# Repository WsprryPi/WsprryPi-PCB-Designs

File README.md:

# WsprryPi PCB Designs

KiCad schematics, PCB layouts, local libraries, and engineering documentation for WsprryPi and Raspberry Pi Pico projects.

See each project's order status, assembly requirements, and validation limits before fabrication. KiCad source files are authoritative; included PDFs are reference exports and may not match the current sources.

## Experimental use and warranty

All designs are provided **as is, without warranty**, as stipulated by the [MIT license](LICENSE.md) for repository-owned work. These are experimental hardware systems. They should not be used for production work unless the operator understands the design's limitations, assembly and power requirements, calibration needs, and the validation required for the actual system and operating conditions.

The operator is responsible for determining suitability and verifying the assembled hardware. A clean CAD check or a fabrication-ready layout does not establish electrical, RF, thermal, mechanical, or system performance. Third-party assets retain their documented licenses and notices.

## Projects

| Project | Purpose | Status / reference export |
| --- | --- | --- |
| [WsprryPi LPF](WsprryPi%20LPF/README.md) | Low-pass filter board and design workbook | Export from the KiCad source |
| [WsprryPi LPF-LCL](WsprryPi%20LPF-LCL/README.md) | Five-element L-first LPF with minimum-loss WSPR/QRSS tuning | Independent routed development board; physical/RF qualification pending |
| [Relay-Switched LPF](Relay-Switched%20LPF/README.md) | Independent reconstruction of the QRP Labs Rev. 5 five-filter relay carrier | Schematic and two-layer PCB; unqualified, see project validation |
| [Pico 2W Wattmeter Shield](Pico%202W%20Wattmeter%20Shield/README.md) | ADL5904 RF detector and ADS1115 ADC shield | See project assembly drawings |
| [Pico 2W Shield Template](Pico%202W%20Shield%20Template/README.md) | Unwired shield interface, outline, and antenna notch | KiCad project template |
| [Logic RF Driver](Logic%20RF%20Driver/README.md) | Compact SN74LVC2T45 clock driver with paralleled outputs | Routed two-layer prototype for the 137 kHz–145 MHz target; RF performance unqualified |
| [RF Indicator LED](RF%20Indicator%20LED/README.md) | RF indicator circuit draft | Incomplete component selection; empty PCB, see project validation |
| [Quad Logic Buffer Amp](Quad%20Logic%20Buffer%20Amp/README.md) | Logic buffer RF amplifier schematic | Standalone 80 × 30 mm estimated PCB, placed and unrouted |
| [WsprryPico Quad Logic Buffer Amp](WsprryPico%20Quad%20Logic%20Buffer%20Amp/README.md) | Independent Pico shield copy of Quad Logic Buffer Amp with project-local libraries | Placement review pending, unrouted |
| [WsprryPi Quad Logic Buffer Amp](WsprryPi%20Quad%20Logic%20Buffer%20Amp/README.md) | Raspberry Pi Zero HAT logic buffer amplifier with local LPF header assets | Placement review pending, unrouted |
| [WsprryPico GPIO Shield with GPS](WsprryPico%20GPIO%20Shield%20with%20GPS/README.md) | Direct Pico GP2 BS170 RF amplifier with onboard GNSS and independent local libraries | Placed and routed GPIO/GNSS design; see current validation |
| [WsprryPico GPIO Shield with GPS - Torroid Edition](WsprryPico%20GPIO%20Shield%20with%20GPS%20-%20Torroid%20Edition/README.md) | GPIO amplifier with a bifilar transformer | Placed and routed within the original outline; all SMT on the underside; physical/RF qualification pending |
| [WsprryPico Synth Shield with GPS](WsprryPico%20Synth%20Shield%20with%20GPS/README.md) | Pico 2 W TCXO/Si5351A shield with a BS170 amplifier and onboard GNSS | Implemented PCB for the 2200 m–10 m target; see current validation and bias setup |
| [QRP Labs Modules](QRP%20Labs%20Modules/README.md) | Electrical models of the photographed 25 MHz TCXO and Rev6 synthesizer, with their interconnection | [Reference schematic PDF](QRP%20Labs%20Modules/QRP%20Labs%20Modules.pdf); separate from the proposed synth shield |
| [RPi Full-Size HAT Template](RPi%20Full-Size%20HAT%20Template/README.md) | Official full-size HAT geometry and complete 40-pin interface | KiCad project template |
| [RPi Zero HAT Template](RPi%20Zero%20HAT%20Template/README.md) | Zero-size uHAT geometry and complete HAT+ capable 40-pin interface | KiCad project template |
| [WsprryPi Zero GPIO BS170](WsprryPi%20Zero%20GPIO%20BS170/README.md) | Zero-size Raspberry Pi GPIO RF amplifier with a single BS170 | **Ready for order:** headers and BS170 fitted by hand after manufacture; see [fabrication and assembly notes](WsprryPi%20Zero%20GPIO%20BS170/FABRICATION-NOTES.md) |

[Project-local Pico 2 W library assets](Pico%202W%20Wattmeter%20Shield/pico-2w-libs/README.md) include a symbol, footprints, and STEP model with documented compatibility and provenance limits. They are stored inside the Wattmeter Shield project; the Shield Template uses its own independent local libraries.

## Open a design

Clone [WsprryPi/WsprryPi-PCB-Designs](https://github.com/WsprryPi/WsprryPi-PCB-Designs) into a folder named `WsprryPi PCB Designs` and open the project's `.kicad_pro` file in KiCad. Read its README for assembly requirements, dependencies, and validation limits. Follow the applicable template's instructions to create a new shield or HAT project.

| Project | Saved schematic and PCB generator version |
| --- | --- |
| WsprryPi LPF, WsprryPi LPF-LCL, Pico 2W Wattmeter Shield, Pico 2W Shield Template, Logic RF Driver, RF Indicator LED, Quad Logic Buffer Amp, WsprryPico Quad Logic Buffer Amp, WsprryPi Quad Logic Buffer Amp, WsprryPico GPIO Shield with GPS, WsprryPico GPIO Shield with GPS - Torroid Edition, WsprryPico Synth Shield with GPS, RPi Full-Size HAT Template, RPi Zero HAT Template, WsprryPi Zero GPIO BS170 | KiCad 10.0 |

Project library tables use `${KIPRJMOD}` paths. Keep each project's local libraries together when copying it. The Pico and HAT projects use their own local libraries and installed KiCad models where their project documentation specifies them.

### Project-local libraries

The LPF includes local copies of its symbols and footprints, plus available STEP models, resolved through `${KIPRJMOD}`. Its local library assets require KiCad 10.0.1 or newer; the generator version above describes its saved format. The other projects maintain their own independent local libraries as described in their READMEs.

- [LPF library contents and limits](WsprryPi%20LPF/libraries/README.md)
- [BS170 amplifier library sources and limits](WsprryPi%20Zero%20GPIO%20BS170/LIBRARY-SOURCES.md)

Project documentation records model gaps, assembly exclusions, and the applicability of ERC/DRC findings to the identified source revision. Order readiness does not establish measured electrical, thermal, or RF performance.

## Design proposals

These documents describe proposed circuits and outstanding engineering requirements; they do not establish implemented or validated hardware.

- [GPS frequency calibration for Pi and Pico](design/GPS-FREQUENCY-CALIBRATION.md): LS7366R capture of Si5351 CLK2 against GPS PPS.
- [Broadband RF amplifier HAT](design/raspberry-pi-hat-broadband-rf-amplifier.md): a proposed clock-input amplifier, power control, and supply architecture.

## Repository contents

Track design sources, local libraries, reusable models, design calculations, intentional reference exports, and documentation. Preserve legacy cache or rescue libraries required by a design.

The root [`.gitignore`](.gitignore) covers KiCad local preferences, locks, caches, automatic backups, `.history`, and `jlcpcb/` plugin state and output throughout the repository. Put regenerable exports in `generated/`, `production/`, or `fabrication/`.

Publish manufacturing packages with the corresponding GitHub release, identifying the source commit, board revision, KiCad version, and validation status. Keep assembly and fabrication requirements in the project's maintained documentation.

## Contributions and license

See [CONTRIBUTING.md](CONTRIBUTING.md) for editing and validation requirements. Report problems through [GitHub Issues](https://github.com/WsprryPi/WsprryPi-PCB-Designs/issues). [AGENTS.md](AGENTS.md) contains shared agent guidance; [CLAUDE.md](CLAUDE.md) points to it.

Repository-owned work uses the [MIT license](LICENSE.md). Preserve third-party copyright, attribution, and license terms; project and library documentation identifies known exceptions and provenance limits.

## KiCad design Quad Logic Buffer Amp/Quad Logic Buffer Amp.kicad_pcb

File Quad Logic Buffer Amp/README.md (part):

# Quad Logic Buffer Amp

The drawing uses native symbols, 375 wire segments, branch junctions, and common VDD and GND power symbols. J2 and R6 connect the isolated output return to circuit ground as drawn. U1, U2, U4, and U5 use the reference symbol layout and the local TSSOP-20 footprint. The printed supplier code C6930 identifies [TI SN74ACT244PWR](https://www.lcsc.com/product-detail/C6930.html). The connector and RGB LED symbols reproduce the visible terminal functions. Their physical pin assignments and package selections are recorded below.

## Standalone PCB

The [PCB](Quad%20Logic%20Buffer%20Amp.kicad_pcb) uses an estimated **80 × 30 mm** rectangular outline. The finished instrument is specified as 85 × 30 × 45 mm. Page 4 shows the bare board nearly overhead. In a 1,650-pixel-high rendering, the board spans about 670 × 255 pixels and the USB-C shell spans about 75 pixels. Using the selected shell’s 8.94 mm nominal width gives about 80 × 30.4 mm. The roughly 2.6:1 board aspect ratio also matches the chosen outline. Shell variation, perspective, and edge selection limit the estimate to a few millimetres. The photo shows no distinct mounting holes. The PCB has a 1 mm fillet at each corner. [Product specifications](https://turnislandsystems.com/product/tis-1w-digital-1w-power-amplifier/) · [Board photograph and rendering, page 4](https://turnislandsystems.com/wp-content/uploads/2025/09/TIS-1W.pdf#page=4)

## Independent local library

The [symbol table](sym-lib-table) and [footprint table](fp-lib-table) register `logic-buffer-amp`. Every library and assigned 3D-model path uses `${KIPRJMOD}`; neither source project nor an installed KiCad 3D-model library is needed to resolve these copied assets.

- [Symbol library](logic-buffer-amp.kicad_sym): unused template symbols `Raspberry_Pi_Pico_2W` and `Socket_1x20_P2.54mm_BOM`, plus synth-shield `C`, `GND`, `L`, `LED`, `PWR_FLAG`, `R`, and `SMA`, and a standalone `SN74ACT244`.
- [Footprint library](logic-buffer-amp.pretty/): the template header and all synth-shield capacitor, inductor, LED, resistor, and SMA footprint variants listed below, plus the TSSOP-20 buffer footprint.
- [3D models](logic-buffer-amp.3dshapes/README.md): twenty-three local assets, including local copies of the standard models referenced by the synth shield.
- [Sources, terms, and limitations](LIBRARY-SOURCES.md) and [asset manifest](LIBRARY-MANIFEST.json).

| Symbol | Available local footprints |
| --- | --- |
| Raspberry_Pi_Pico_2W | Raspberry_Pi_Pico_2W_Header |
| Socket_1x20_P2.54mm_BOM | None; schematic-only purchasing description |
| C | C_0603_1608Metric, C_0805_2012Metric, C_1206_3216Metric |
| L | L_0603_1608Metric, L_TDK_VLS6045EX_VLS6045AF |
| LED | LED_0603_1608Metric |
| R | R_0603_1608Metric, R_1210_3225Metric |
| SMA | SMA_Adafruit_1865_EdgeMount |
| SN74ACT244 | TSSOP-20_4.4x6.5mm_P0.65mm (TI PW package) |
| GND, PWR_FLAG | None; schematic-only power symbols |

The `SN74ACT244` symbol defaults to the local TSSOP-20 footprint for **SN74ACT244PWR** (TI PW package, 4.4 x 6.5 mm body, 0.65 mm pitch). Its 20 pin names and electrical types were checked against [TI SCAS517G, page 3](https://www.ti.com/lit/ds/symlink/sn74act244.pdf#page=3). The installed KiCad 74HC244 graphics were adapted into a standalone ACT definition, with TI pin naming and datasheet; this is not a simulation model. Other imported symbols retain their source defaults. Assign the appropriate `logic-buffer-amp` footprint when placing a component; generic symbols do not select a particular physical part. The placed schematic assignments and remaining package decisions are listed below.

## Footprints and models

All 65 physical references, including five paired test-point footprints providing ten probe pads, have project-local footprints. The schematic-only power symbols are outside this count. KiCad 10.0.6 netlist verification confirmed that every assigned symbol has the same set of pin numbers as the footprint pads and that every populated package resolves to a local model. The ten bare test pads have no component body. The footprint update preserved net connectivity.

| Assigned references | Local package and model |
| --- | --- |
| C2, all 100 nF capacitors, and all 0603 resistors | See the [passive BOM](#passive-bom) below. |
| U1, U2, U4, U5 | TI PW TSSOP-20, matching KiCad package STEP |
| L1 | Murata BLM18PG121SN1D, 0603 power-line ferrite bead, 120 Ω ±25% at 100 MHz, 2 A through 85 °C, 50 mΩ maximum initial DC resistance. LCSC reported 832,350 units on 2026-11-18. [LCSC C14709](https://www.lcsc.com/product-detail/C14709.html) · [Murata specification](https://pim.murata.com/asset/pim4/ferriteBeadInductortypefilter/ENFA2345_PDF_FERRITEBEADINDUCTORTYPEFILTER) |
| J5, J6 | Adafruit product 1865 female edge-launch SMA for a 1.6 mm board. Both connectors are on hand. Local VRML is an illustrative preview. [Connector specification](https://www.adafruit.com/product/1865) |
| J1, J2 | Vertical 1×2 through-hole pin header on 2.54 mm pitch, with the Zero GPIO BS170 shield’s footprint and STEP model |
| Z6 | Nexperia PESD5V0U1UA,115 in SOD323. Pad 1 is cathode and pad 2 is anode. [Manufacturer pinning](https://assets.nexperia.com/documents/data-sheet/PESD5V0U1UA.pdf) |
| R9 | Panasonic ERJP14J510U, 51 Ω, ±5%, 0.5 W rated, 1210. The permissible continuous input depends on board temperature and derating. [Manufacturer specifications](https://industrial.panasonic.com/tw/products/pt/small-and-high-power-chip-resistors/models/ERJP14J510U) |
| TP22, TP4, TP21, TP10, TP6 | [Paired probe footprint](logic-buffer-amp.pretty/TestPoint_Pair_P2.54mm_Drill0.5mm.kicad_mod) with two of the same pads at a fixed 2.54 mm pitch. Each pair uses one reference. Schematic units A and B correspond to pads 1 and 2. TP22 is USB5V/GND (formerly TP22/TP3), TP4 is D+/D− (formerly TP4/TP5), and TP21 is VDD/GND (formerly TP21/TP19). TP10 is RF input/GND (formerly TP10/TP16). TP6 is RF output/GND_OUT (formerly TP6/TP7). On each RF pair, pad 1 is toward the rear and pad 2 is toward the SMA edge. |
| U6 | TI SN74LVC2G14DCKR, six-pin SC70. Inputs 1/3, outputs 6/4, GND 2, VCC 5. [TI pinout](https://www.ti.com/lit/ds/symlink/sn74lvc2g14.pdf) |
| U88 | TI SN74LVC1G00DCKR, five-pin SC70. Inputs 1/2, GND 3, output 4, VCC 5. [TI pinout](https://www.ti.com/lit/ds/symlink/sn74lvc1g00.pdf) |
| U8, U59 | TI SN74LVC2G04DCKR, six-pin SC70. Inputs 1/3, outputs 6/4, GND 2, VCC 5. [TI pinout](https://www.ti.com/lit/ds/symlink/sn74lvc2g04.pdf) |
| D3 | Diodes Incorporated 1N4148W-7-F in SOD-123. Banded cathode on pad 1, anode on pad 2. [Manufacturer datasheet](https://www.diodes.com/datasheet/download/1N4148W.pdf) |
| Q3 | onsemi MMBT3904LT1G, SOT-23. Base 1, emitter 2, collector 3. [onsemi pinout](https://www.onsemi.com/pdf/datasheet/mmbt3904lt1-d.pdf) |
| Q6 | Vishay Si2343DS-T1-GE3, SOT-23. Gate 1, source 2, drain 3. [Vishay pinout](https://www.vishay.com/docs/72079/si2343ds.pdf) |

### Passive BOM

Quantities are per board. Both Samsung capacitor types are X7R, ±10%, 50 V DC. C2 is a 1206 bulk capacitor on the 5 V rail after L1. The twelve general-purpose 100 nF positions use Samsung 0603 X7R capacitors. The four bridge coupling capacitors use Walsin 1206 C0G/NP0, ±5%, 50 V DC. The thirteen 0603 resistors are UNI-ROYAL thick film, ±1%, 100 mW, 75 V maximum working voltage, and ±100 ppm/°C. Both power and voltage limits apply. R9 uses the separately specified 0.5 W 1210 input termination. Stock was checked at LCSC on 2026-11-18.

| References | Qty | Value | Manufacturer part number | LCSC | Stock |
| --- | ---: | --- | --- | --- | ---: |
| C2 | 1 | 1 µF | CL31B105KBHNNNE | [C1848](https://www.lcsc.com/product-detail/C1848.html) | 141,650 |
| C5–C7, C9, C14, C15, C21, C22, C34, C127, C128, C160 | 12 | 100 nF | CL10B104KB8NNNC | [C1591](https://www.lcsc.com/product-detail/C1591.html) | 214,300 |
| C10–C13 | 4 | 100 nF | 1206N104J500CT | [C170182](https://www.lcsc.com/product-detail/C170182.html) | 119,055 |
| R2, R3 | 2 | 51 Ω | 0603WAF510JT5E | [C23197](https://www.lcsc.com/product-detail/C23197.html) | 650,600 |
| R37 | 1 | 100 Ω (production marking 01A) | TBD | — | — |
| R30, R31 | 2 | 5.1 kΩ | 0603WAF5101T5E | [C23186](https://www.lcsc.com/product-detail/C23186.html) | 13,449,700 |
| R4, R5, R8, R13, R19, R36 | 6 | 10 kΩ | 0603WAF1002T5E | [C25804](https://www.lcsc.com/product-detail/C25804.html) | 2,287,600 |
| R10 | 1 | 100 kΩ | 0603WAF1003T5E | [C25803](https://www.lcsc.com/product-detail/C25803.html) | 4,436,200 |
| R6 | 1 | 1 MΩ | 0603WAF1004T5E | [C22935](https://www.lcsc.com/product-detail/C22935.html) | 2,087,900 |

C10/C11 and C12/C13 are the two bridge coupling pairs. At 1 W into 50 Ω, the ideal 1:2 transformer reflects 12.5 Ω and carries 0.283 A RMS of load current in its primary. Each matched parallel pair splits that current, giving 0.141 A RMS per capacitor. As a design check, 0.25 A RMS per capacitor allows margin for magnetizing current and unequal sharing. At 1 MHz the two 200 nF pairs contribute about 1.59 Ω of ideal series reactance around the loop.

The bridge uses a Class I C0G dielectric for capacitance stability and low dielectric loss. Verify loaded output and capacitor temperature with these parts at the intended duty cycle across 1–60 MHz.

L1 sits between the protected USB supply at Q6 and the amplifier VDD rail, with C14 on the input side and C2 on the load side. The reference amplifier drew 364–400 mA into 50 Ω at the three documented frequencies (1, 10, and 60 MHz) and 488 mA into 25 Ω at 10 MHz. At 488 mA, the maximum initial DC resistance gives a 24.4 mV drop and 11.9 mW of DC loss. Murata’s typical impedance curve rises from a few ohms at 1 MHz to roughly 40 Ω at 10 MHz and 100 Ω at 60 MHz. This favors isolation of fast driver currents from the USB lead. Actual attenuation depends on DC bias, the capacitors, and the routed board. [Murata impedance curve, page 3](https://datasheet.octopart.com/BLM18PG121SN1D-Murata-datasheet-138707164.pdf#page=3)

The bead body is nominally 1.6 × 0.8 × 0.8 mm. The project’s generic 0603 pattern and Murata’s reflow pattern both have a 0.70 mm inner gap. The project uses a 2.45 mm outer span and 0.95 mm pad width, compared with Murata’s 2.0 mm span and 0.7 mm exposed width. The current rating and DC-drop calculation apply to the bead. The local STEP is a nominal package preview. [Murata mounting drawing, page 9](https://pim.murata.com/asset/pim4/ferriteBeadInductortypefilter/ENFA2345_PDF_FERRITEBEADINDUCTORTYPEFILTER#page=9)

D4 and D5 use CHONGTIAN CT-3210URGBC-P15-2B side-view RGB LEDs. With the lens facing the board edge (local −Y), the four lands read left to right as 1 red, 4 green, 3 blue, and 2 common anode. Both anodes go to VDD. D4 uses blue through R8. The D5 driver connects the two inner cathodes via R15 and R13 as detailed below. The local footprint follows the recommended 3.9 mm land span. The local 3D model represents the nominal body and side lens. LCSC listed 2,450 units on 2026-11-18. [LCSC C52676076](https://www.lcsc.com/product-detail/C52676076.html) · [Manufacturer drawing, PDF page 2](https://datasheet.lcsc.com/datasheet/pdf/34cd5fd2fc904333a2eb28493617a30e.pdf#page=2)

X1 uses the HRO TYPE-C-31-M-12 horizontal top-mount USB-C receptacle. The drawing combines A1/B12 and B1/A12 into two ground lands and A4/B9 and B4/A9 into two VBUS lands. A6/B6 are D+, A7/B7 are D−, A5 is CC1, B5 is CC2, and A8/B8 are the open SBU contacts. All four shell stakes use SH on GND. The two locating holes are unplated. The local footprint uses the paired land names in the schematic and a supplier 3D model. LCSC listed 491,060 units on 2026-11-18. [LCSC C165948](https://www.lcsc.com/product-detail/C165948.html) · [Manufacturer drawing](https://datasheet.lcsc.com/datasheet/pdf/9e56b777c022540fcce7c7f67825f55e.pdf)

Page 3 specifies SC70 for U8 and U59. In the page 4 prototype photograph, U6 and U88 have the same apparent body size and lead pitch as those adjacent inverters. The corresponding TI DCK packages preserve the schematic pin numbers. The visible size of D3 relative to Q3 and nearby 0603 passives supports SOD-123. The selected ordering codes are implementation choices for this shield.

### L2 flat-mount transformer

The [four-pad footprint](logic-buffer-amp.pretty/Transformer_BN43-1502_Flat_4Lead.kicad_mod) and [VRML model](logic-buffer-amp.3dshapes/Transformer_BN43-1502_Flat_4Lead.wrl) mount the BN43-1502 flat with both bores parallel to the board. Page 3 specifies an isolated 1:2 turns ratio. Page 4 shows two winding ends emerging at each end of the core. The footprint assigns the primary to the negative-Y end and the secondary to the positive-Y end. Left and right below refer to the top view at zero footprint rotation.

| Pad | Center X, Y (mm) | Winding and schematic connection |
| --- | --- | --- |
| 1, square | −3.25, −8.75 | Primary, C12.2 and C13.2, also R37.1 |
| 2 | +3.25, −8.75 | Primary, C10.2 and C11.2 |
| 3 | −3.25, +8.75 | Secondary output, TP6 pad 1 and J5 center contact |
| 4 | +3.25, +8.75 | Secondary return, TP6 pad 2 and J5 shield on GND_OUT |

L2 uses the builder-confirmed BN43-1502 with two primary turns and four secondary turns. A 50 Ω secondary load reflects 12.5 Ω to the bridge. Production wire gauge is unknown. The model shows each turn passing through both bores, with separate winding ends at the measured hole positions.

**Winding and installation**

1. Lay the core flat in its footprint orientation. Call the end facing pads 1 and 2 the primary face and the opposite end the secondary face. Label the **whole bore** beside pads 1 and 3 **A**, and the bore beside pads 2 and 4 **B**. Keep these labels fixed when working from the other end. One turn goes out through one bore and returns through the other.
2. **Primary, pad 1 to pad 2:** Leave a tail at pad 1. Feed the wire through A from the primary face to the secondary face, then back through B to the primary face. Repeat that complete path once. The finish exits B beside pad 2.
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
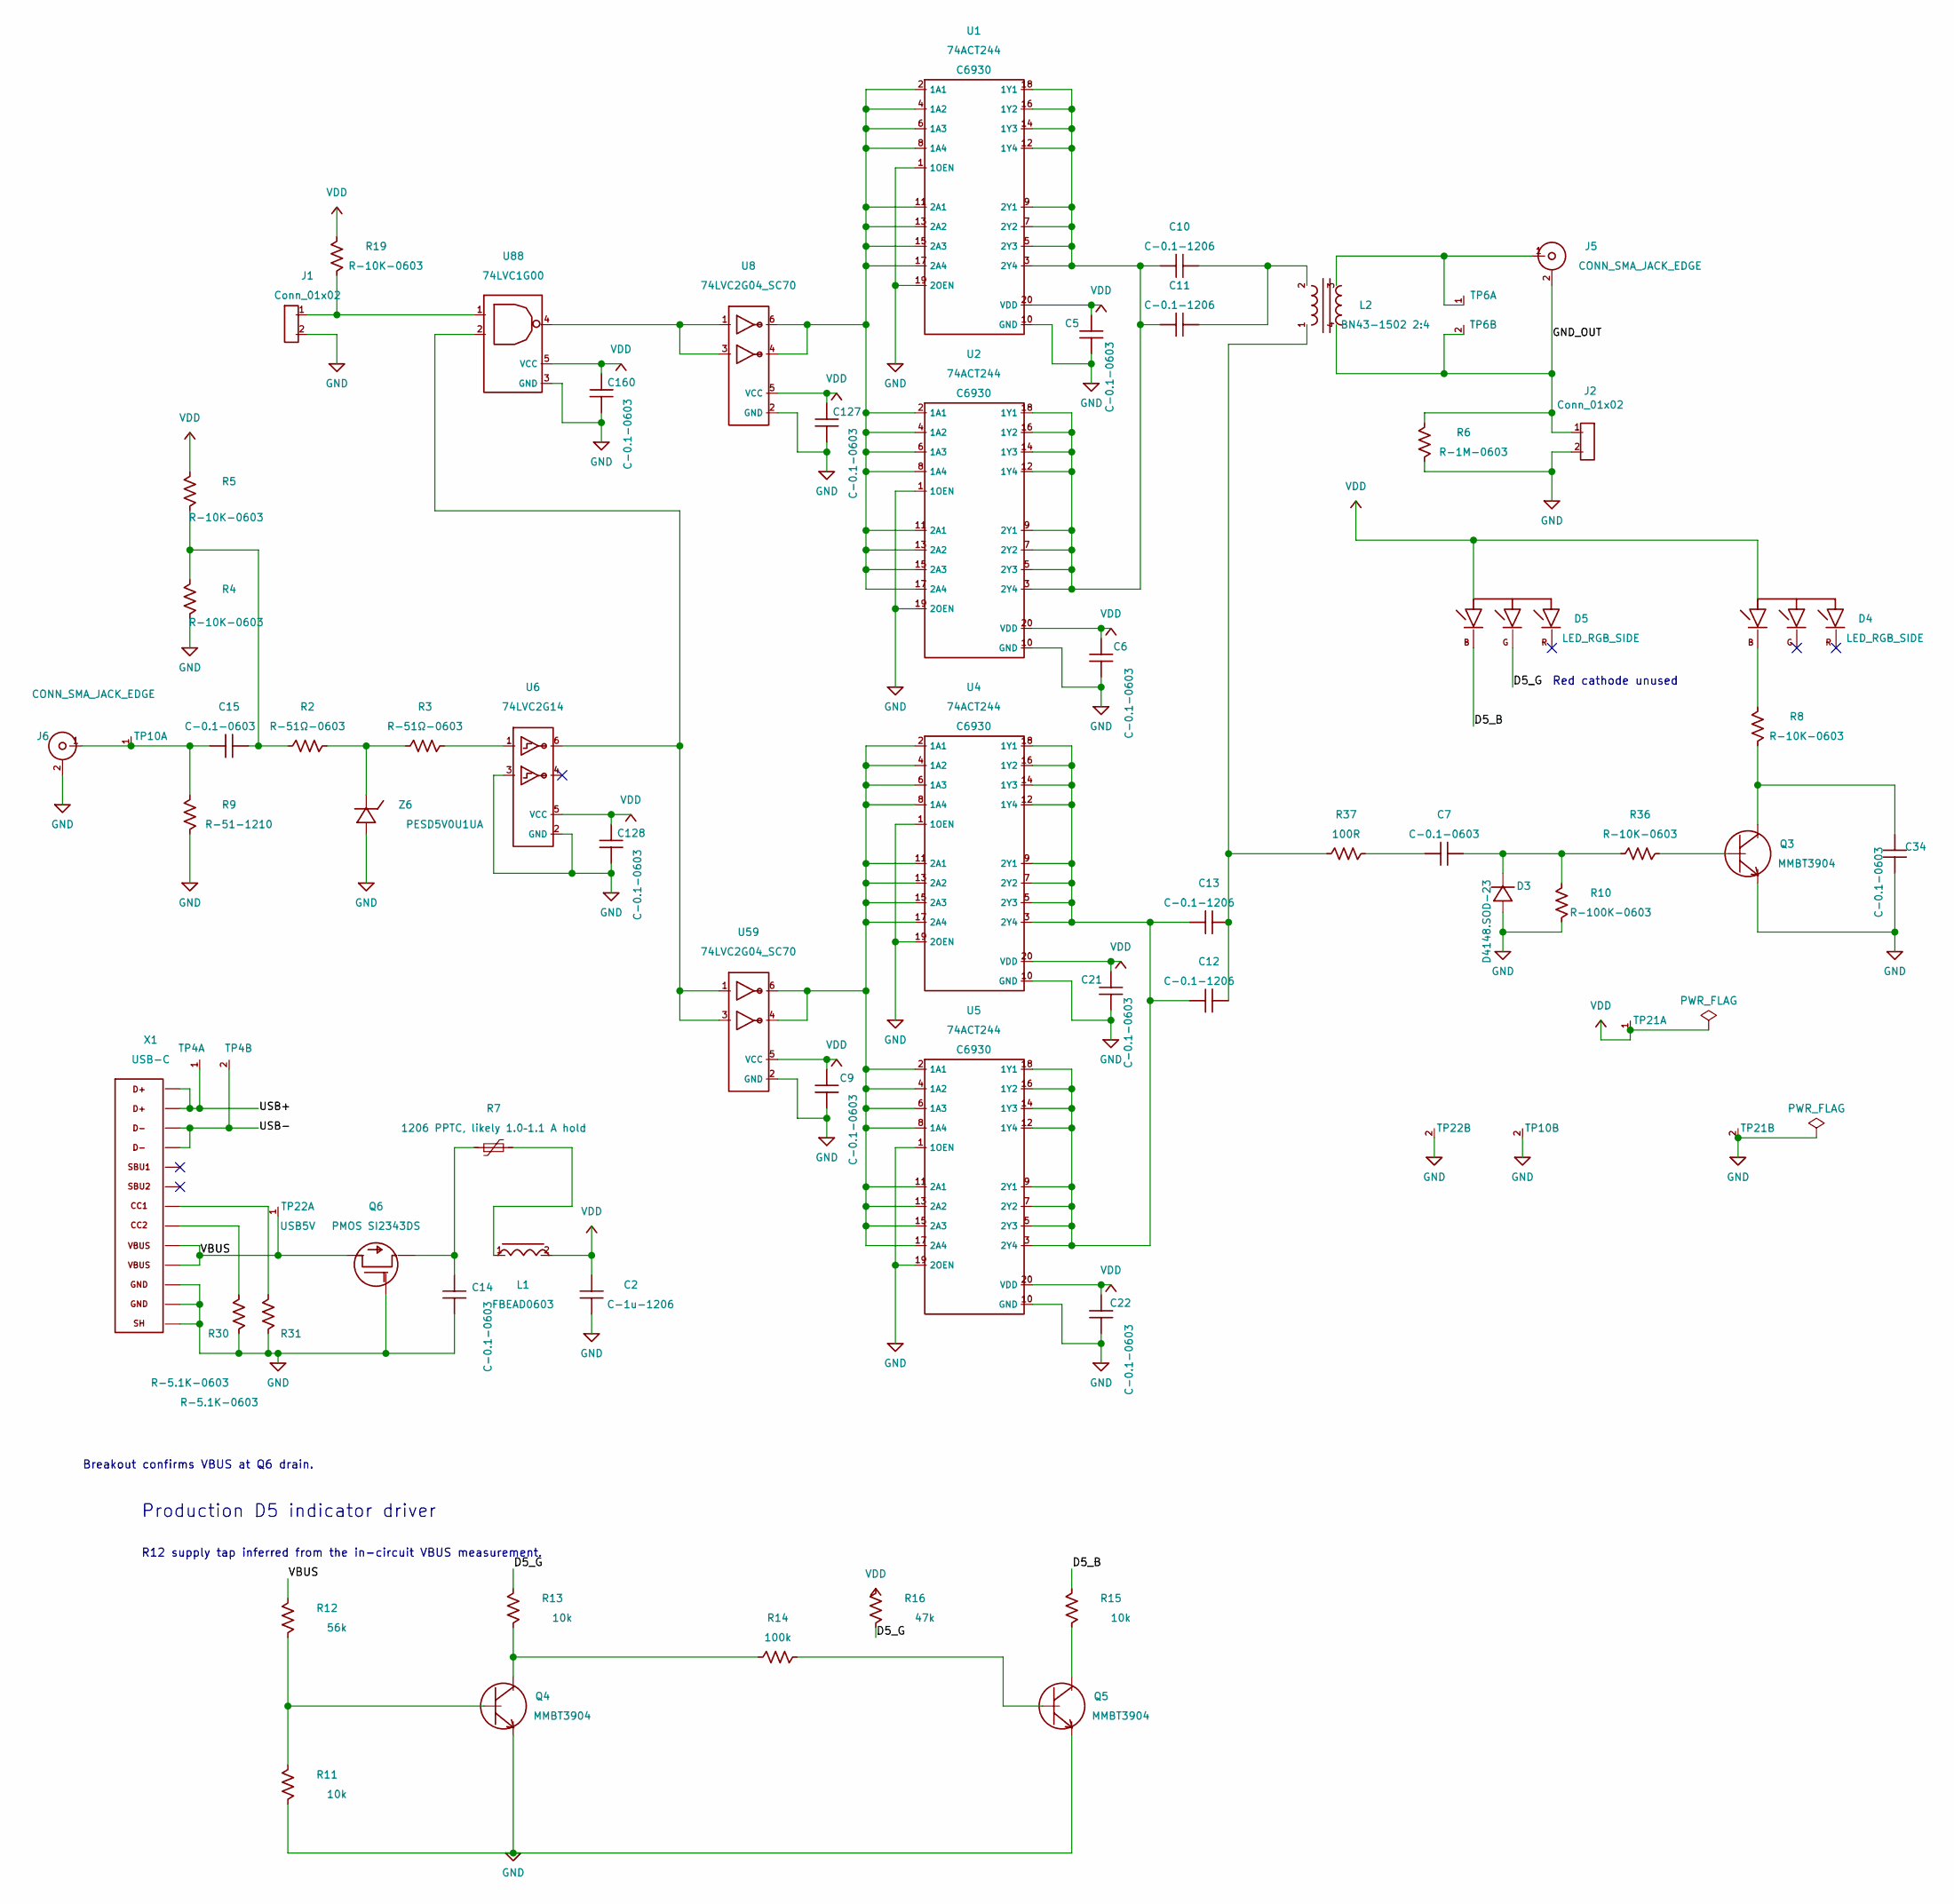
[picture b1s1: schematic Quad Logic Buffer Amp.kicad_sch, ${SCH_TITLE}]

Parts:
C2: C-1u-1206; C_1206_3216Metric; MPN CL31B105KBHNNNE; LCSC C1848
C5, C6, C7, C9, C14, C15, C21, C22, C34, C127, C128, C160: C-0.1-0603; C_0603_1608Metric; MPN CL10B104KB8NNNC; LCSC C1591
C10, C11, C12, C13: C-0.1-1206; C_1206_3216Metric; MPN 1206N104J500CT; LCSC C170182
D3: D4148.SOD-23; D_SOD-123; MPN 1N4148W-7-F
D4, D5: LED_RGB_SIDE; LED_CT-3210URGBC-P15-2B; MPN CT-3210URGBC-P15-2B; LCSC C52676076
J1, J2: Conn_01x02; PinHeader_1x02_P2.54mm_Vertical
J5, J6: CONN_SMA_JACK_EDGE; SMA_Adafruit_1865_EdgeMount
L1: FBEAD0603; L_0603_1608Metric; MPN BLM18PG121SN1D; LCSC C14709
L2: BN43-1502 2:4; Transformer_BN43-1502_Flat_4Lead
Q3: MMBT3904; SOT-23; MPN MMBT3904LT1G
Q4, Q5: MMBT3904; SOT-23
Q6: PMOS SI2343DS; SOT-23; MPN Si2343DS-T1-GE3
R2, R3: R-51Ω-0603; R_0603_1608Metric; MPN 0603WAF510JT5E; LCSC C23197
R4, R5, R8, R19, R36: R-10K-0603; R_0603_1608Metric; MPN 0603WAF1002T5E; LCSC C25804
R6: R-1M-0603; R_0603_1608Metric; MPN 0603WAF1004T5E; LCSC C22935
R7: 1206 PPTC, likely 1.0–1.1 A hold; Fuse_1206_3216Metric
R9: R-51-1210; R_1210_3225Metric; MPN ERJP14J510U
R10: R-100K-0603; R_0603_1608Metric; MPN 0603WAF1003T5E; LCSC C25803
R11, R13, R15: 10k; R_0603_1608Metric; MPN 0603WAF1002T5E; LCSC C25804
R12: 56k; R_0603_1608Metric
R14: 100k; R_0603_1608Metric
R16: 47k; R_0603_1608Metric
R30, R31: R-5.1K-0603; R_0603_1608Metric; MPN 0603WAF5101T5E; LCSC C23186
R37: 100R; R_0603_1608Metric
TP4: USB data; TestPoint_Pair_P2.54mm_Drill0.5mm
TP6: RF output; TestPoint_Pair_P2.54mm_Drill0.5mm
TP10: RF input; TestPoint_Pair_P2.54mm_Drill0.5mm
TP21: VDD/GND; TestPoint_Pair_P2.54mm_Drill0.5mm
TP22: USB5V; TestPoint_Pair_P2.54mm_Drill0.5mm
U1, U2, U4, U5: 74ACT244; TSSOP-20_4.4x6.5mm_P0.65mm; LCSC C6930
U6: 74LVC2G14; SOT-363_SC-70-6; MPN SN74LVC2G14DCKR
U8, U59: 74LVC2G04_SC70; SOT-363_SC-70-6; MPN SN74LVC2G04DCKR
U88: 74LVC1G00; SOT-353_SC-70-5; MPN SN74LVC1G00DCKR
X1: USB-C; USB_C_Receptacle_HRO_TYPE-C-31-M-12; MPN TYPE-C-31-M-12; LCSC C165948
Z6: PESD5V0U1UA; D_SOD-323; MPN PESD5V0U1UA,115

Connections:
/D5_B: D5.3 (B), R15.1
/D5_G: D5.4 (G), R13.1, R16.2
/GND_OUT: J2.1, J5.2, L2.4, R6.1, TP6.2
/USB+: TP4.1, X1.A6, X1.B6
/USB-: TP4.2, X1.A7, X1.B7
/VBUS: Q6.3 (D), R12.1, TP22.1, X1.A4B9 (VBUS1), X1.B4A9 (VBUS2)
GND: C2.2, C5.2, C6.2, C9.2, C14.2, C21.2, C22.2, C34.2, C127.2, C128.2, C160.2, D3.2 (A), J1.2, J2.2, J6.2, Q3.2 (E), Q4.2 (E), Q5.2 (E), Q6.1 (G), R4.2, R6.2, R9.2, R10.2, R11.2, R30.2, R31.2, TP10.2, TP21.2, TP22.2, U1.1 (1OEN), U1.10 (GND), U1.19 (2OEN), U2.1 (1OEN), U2.10 (GND), U2.19 (2OEN), U4.1 (1OEN), U4.10 (GND), U4.19 (2OEN), U5.1 (1OEN), U5.10 (GND), U5.19 (2OEN), U6.2 (GND), U6.3, U8.2 (GND), U59.2 (GND), U88.3 (GND), X1.A1B12 (GND1), X1.B1A12 (GND2), X1.SH (SHELL), Z6.2 (A)
unnamed: C7.1, R37.2
unnamed: C10.2, C11.2, L2.2
unnamed: C12.2, C13.2, L2.1, R37.1
unnamed: C15.2, R2.1, R4.1, R5.2
unnamed: C7.2, D3.1 (K), R10.1, R36.1
unnamed: D4.3 (B), R8.1
unnamed: J1.1, R19.2, U88.1
unnamed: L1.1, R7.2
unnamed: Q3.1 (B), R36.2
unnamed: C34.1, Q3.3 (C), R8.2
unnamed: Q4.1 (B), R11.1, R12.2
unnamed: Q4.3 (C), R13.2, R14.1
unnamed: Q5.1 (B), R14.2
unnamed: Q5.3 (C), R15.2
unnamed: C14.1, Q6.2 (S), R7.1
unnamed: R3.2, U6.1
unnamed: J5.1, L2.3, TP6.1
unnamed: C15.1, J6.1, R9.1, TP10.1
unnamed: U1.2 (1A1), U1.4 (1A2), U1.6 (1A3), U1.8 (1A4), U1.11 (2A1), U1.13 (2A2), U1.15 (2A3), U1.17 (2A4), U2.2 (1A1), U2.4 (1A2), U2.6 (1A3), U2.8 (1A4), U2.11 (2A1), U2.13 (2A2), U2.15 (2A3), U2.17 (2A4), U8.4, U8.6
unnamed: C10.1, C11.1, U1.3 (2Y4), U1.5 (2Y3), U1.7 (2Y2), U1.9 (2Y1), U1.12 (1Y4), U1.14 (1Y3), U1.16 (1Y2), U1.18 (1Y1), U2.3 (2Y4), U2.5 (2Y3), U2.7 (2Y2), U2.9 (2Y1), U2.12 (1Y4), U2.14 (1Y3), U2.16 (1Y2), U2.18 (1Y1)
unnamed: U4.2 (1A1), U4.4 (1A2), U4.6 (1A3), U4.8 (1A4), U4.11 (2A1), U4.13 (2A2), U4.15 (2A3), U4.17 (2A4), U5.2 (1A1), U5.4 (1A2), U5.6 (1A3), U5.8 (1A4), U5.11 (2A1), U5.13 (2A2), U5.15 (2A3), U5.17 (2A4), U59.4, U59.6
unnamed: C12.1, C13.1, U4.3 (2Y4), U4.5 (2Y3), U4.7 (2Y2), U4.9 (2Y1), U4.12 (1Y4), U4.14 (1Y3), U4.16 (1Y2), U4.18 (1Y1), U5.3 (2Y4), U5.5 (2Y3), U5.7 (2Y2), U5.9 (2Y1), U5.12 (1Y4), U5.14 (1Y3), U5.16 (1Y2), U5.18 (1Y1)
unnamed: U8.1, U8.3, U88.4
unnamed: U6.6, U59.1, U59.3, U88.2
unnamed: R31.1, X1.A5 (CC1)
unnamed: R30.1, X1.B5 (CC2)
unnamed: R2.2, R3.1, Z6.1 (K)
VDD: C2.1, C5.1, C6.1, C9.1, C21.1, C22.1, C127.1, C128.1, C160.1, D4.2 (A), D5.2 (A), L1.2, R5.1, R16.1, R19.1, TP21.1, U1.20 (VDD), U2.20 (VDD), U4.20 (VDD), U5.20 (VDD), U6.5 (VCC), U8.5 (VCC), U59.5 (VCC), U88.5 (VCC)

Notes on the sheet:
Breakout confirms VBUS at Q6 drain.
Red cathode unused
Production D5 indicator driver
R12 supply tap inferred from the in-circuit VBUS measurement.

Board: 2 copper layers, 65 parts (0 on the bottom side), 35 nets, no tracks yet.

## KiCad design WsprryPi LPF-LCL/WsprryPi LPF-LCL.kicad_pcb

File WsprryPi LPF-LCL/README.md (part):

# WsprryPi LPF-LCL

An independent, hand-assembled **five-element L–C–L–C–L low-pass filter**, using a common PCB populated for the selected WSPR/QRSS band. Three coils use the original combined axial-inductor/upright-toroid footprint. Each of the two shunt positions provides two parallel capacitor footprints.

**Status: routed development design, revision 0.1.0; physical assembly and RF performance unverified.** KiCad 10.0.6 ERC, DRC, saved zone refill, and schematic-parity checks pass with no violations or unconnected items. See [validation](VALIDATION.md).

Open [WsprryPi LPF-LCL.kicad_pro](WsprryPi%20LPF-LCL.kicad_pro). All six symbol definitions, four footprint types, and three STEP models and one illustrative SMA VRML model are in independent [project-local libraries](libraries/README.md), using `${KIPRJMOD}` paths. No sibling project is required to open this design or reproduce its numerical models.

## Circuit and band population

```text
RF_IN ── L1 ──┬── L3 ──┬── L5 ── RF_OUT
              │        │
           CA2 || CB2  CA4 || CB4
              │        │
             GND      GND
```

L1 and L5 use the selected row's `L1_L5_H` target; L3 uses `L3_H`. The installed total at **each** shunt position is `C2_C4_F`: `CA2 + CB2 = CA4 + CB4`. `L_END`, `L_MID`, `C_A`, and `C_B` in KiCad are population placeholders, not fixed part values. Select one row from the [minimum-loss component table](model/minimum-loss-values.csv), then record actual parts and measured coils for that assembly. This is one PCB for different band builds, not one fixed population covering every band.

The five-element, 1 dB-ripple Chebyshev response is scaled so its highest-frequency transmission maximum lies at the midpoint of the listed WSPR/QRSS windows. In the ideal real-50 Ω model, the carrier has essentially zero mismatch attenuation, with approximately **42.77 dB attenuation at 2f** and **62.35 dB at 3f**. Coil losses, tolerances, self-resonance, coupling, and PCB parasitics are additional effects; these are not measured results. There is no DC-blocking capacitor.

The [minimum-loss WSPR/QRSS study](model/MINIMUM-LOSS.md) covers frequencies, values, rounding, harmonic tradeoffs, and coil-Q sensitivity. All previous five-element studies, scripts, plots, and numerical results have moved here under [model/](model/README.md), with a local snapshot of the original C-first workbook. The original seven-element comparison is retained for context. Blank QRSS entries for 2200 m and 2 m remain blank. Paired labels such as `30 & 40m` are inherited build identifiers; they do not establish a minimum or adequate harmonic rejection on both bands.

For the 20 m build centered at **14.097000 MHz**, targets are **L1 = L5 = 1.146155 µH**, **L3 = 1.611108 µH**, and **234.3134 pF per shunt position**. A candidate pair is 160 pF + 75 pF per position. These are calculated targets, not purchasing selections or manufacturing tolerances.

## Preserved mechanical interface

Both independent LPF projects now use Adafruit 1865 SMA launches. This project retains the original outline, stackup, headers, and RF axes; the new connector origins are on the board-edge datums:

| Item | Preserved arrangement |
| --- | --- |
| Outline | 45.96 mm long, approximately 12.873 mm high; identical rounded corners and Edge.Cuts primitives |
| Thickness | 1.60 mm saved stackup |
| J1 | Two underside male 1×4 headers as one paired component; 33.02 mm centerline spacing, 2.54 mm pin pitch |
| Input header | Pads 1/4 = GND; 2/3 = RF_IN |
| Output header | Pads 5/8 = GND; 6/7 = RF_OUT |
| J2 input SMA | Adafruit 1865; edge datum (114.00, 99.12) mm, −90° |
| J3 output SMA | Adafruit 1865; edge datum (159.96, 99.12) mm, +90° |

Header geometry, holes, layer, and position match the original. SMA footprints, pad geometry, origins, rotations, and models are now specific to Adafruit 1865. The GND–RF–RF–GND header pinout is **not directly electrically compatible with unmodified QRP Labs LPFs**. Interpret underside contacts by KiCad pad number, not apparent top-view order. A symmetrically populated filter can operate in either direction in a matching WsprryPi socket.

The [Adafruit 1865](https://www.adafruit.com/product/1865) is for 1.6 mm PCBs, matching the saved 1.60 mm stackup. Its independent local footprint has 4.014 mm-long hand-solder lands, a 0.05 mm copper setback, a top RF contact, and ground fingers on both copper faces. There are no paste apertures. A project-local `.kicad_dru` rule permits **0 mm edge clearance only for J2/J3 pads**; all other copper retains the **0.50 mm global requirement**. The physical setback keeps copper clear of the drawn Edge.Cuts stroke. Rule control tests and detailed geometry are in [validation](VALIDATION.md).

The Adafruit footprint derives from its public-domain Eagle `SMA_EDGELAUNCH` package. The local `SMA_Adafruit_1865_Preview.wrl` is illustrative, not supplier CAD. Verify slot tolerance, top/bottom solder access, near-edge copper acceptance by the board fabricator, enclosure clearance, and actual fit. SMA bodies project beyond the board ends; controlled-impedance and RF performance remain unqualified.

## Capacitor mounting

Each of `CA2/CB2` and `CA4/CB4` retains the original strategy:

- For an `A + B` pair, fit one capacitor into each 2.50 mm-pitch footprint. Their sum is the shunt value.
- For one 2.50 mm-pitch capacitor, use pads 1 and 2 of either footprint, leaving the other available for tuning.
- For one 5.00 mm-pitch capacitor, span **CA pad 1 to CB pad 2**, or **CB pad 1 to CA pad 2**. Both combinations measure 5.00 mm. The two signal pads or the two ground pads must not be used as the capacitor terminals.

A spanning capacitor normally occupies both body areas. Check actual body dimensions, lead diameter, neighboring windings, and board edges. Select RF-suitable capacitors and voltage ratings for the intended power; no all-band capacitor family or power rating is qualified.

## Inductor mounting and layout

L1/L3/L5 retain the local `L_Axial_Horiz_Torroid_Vert_12mm_D5mm_P10.2mm` footprint. Its 0.8 mm holes provide two alternatives for each electrical terminal. Fit one winding end to any **pad 1** and the other to any **pad 2**. Same-number holes are connected mounting alternatives. The footprint supports the original axial or upright wound-component strategy, subject to actual lead/body fit.

The generic axial-inductor STEP model does not represent a wound toroid. Select core, turns, wire, measured inductance including leads, Q, self-resonance, power handling, and finished dimensions for each band. Original C-first turn counts do not apply: 2200 m targets reach approximately **117.5 µH at the ends and 165.2 µH at the center**, with physical fit unproven. At 2 m, characterize the assembled RF response rather than relying on low-frequency inductance measurements.

Filter anchors use a **0.25 mm placement grid**, retaining intrinsic pad geometry. J1/J2/J3 are deliberate grid exceptions preserving the mechanical interface. Schematic origins and connections use **1.27 mm / 50 mil**. The PCB retains ground pours on both copper faces, the two capacitor-pair pour keepouts, and stitching. Outer RF paths were rerouted without obsolete end-capacitor branches; small anchor-grid adjustments have repaired copper.

## Assembly and validation

All parts are hand fitted. As inherited, headers, inductors, and capacitors are excluded from default BOM/position outputs; SMAs are included. A default BOM is not a complete purchasing list. No manufacturing package or qualified power rating is supplied.

[VALIDATION.md](VALIDATION.md) records source identity, checks, corrected findings, and remaining work. [scripts/check_project.py](scripts/check_project.py) verifies the mechanical contract, local assets, grids, capacitor spans, and exported netlist topology. Disposable exports belong under ignored `generated/`; final records are under [validation/](validation/).

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
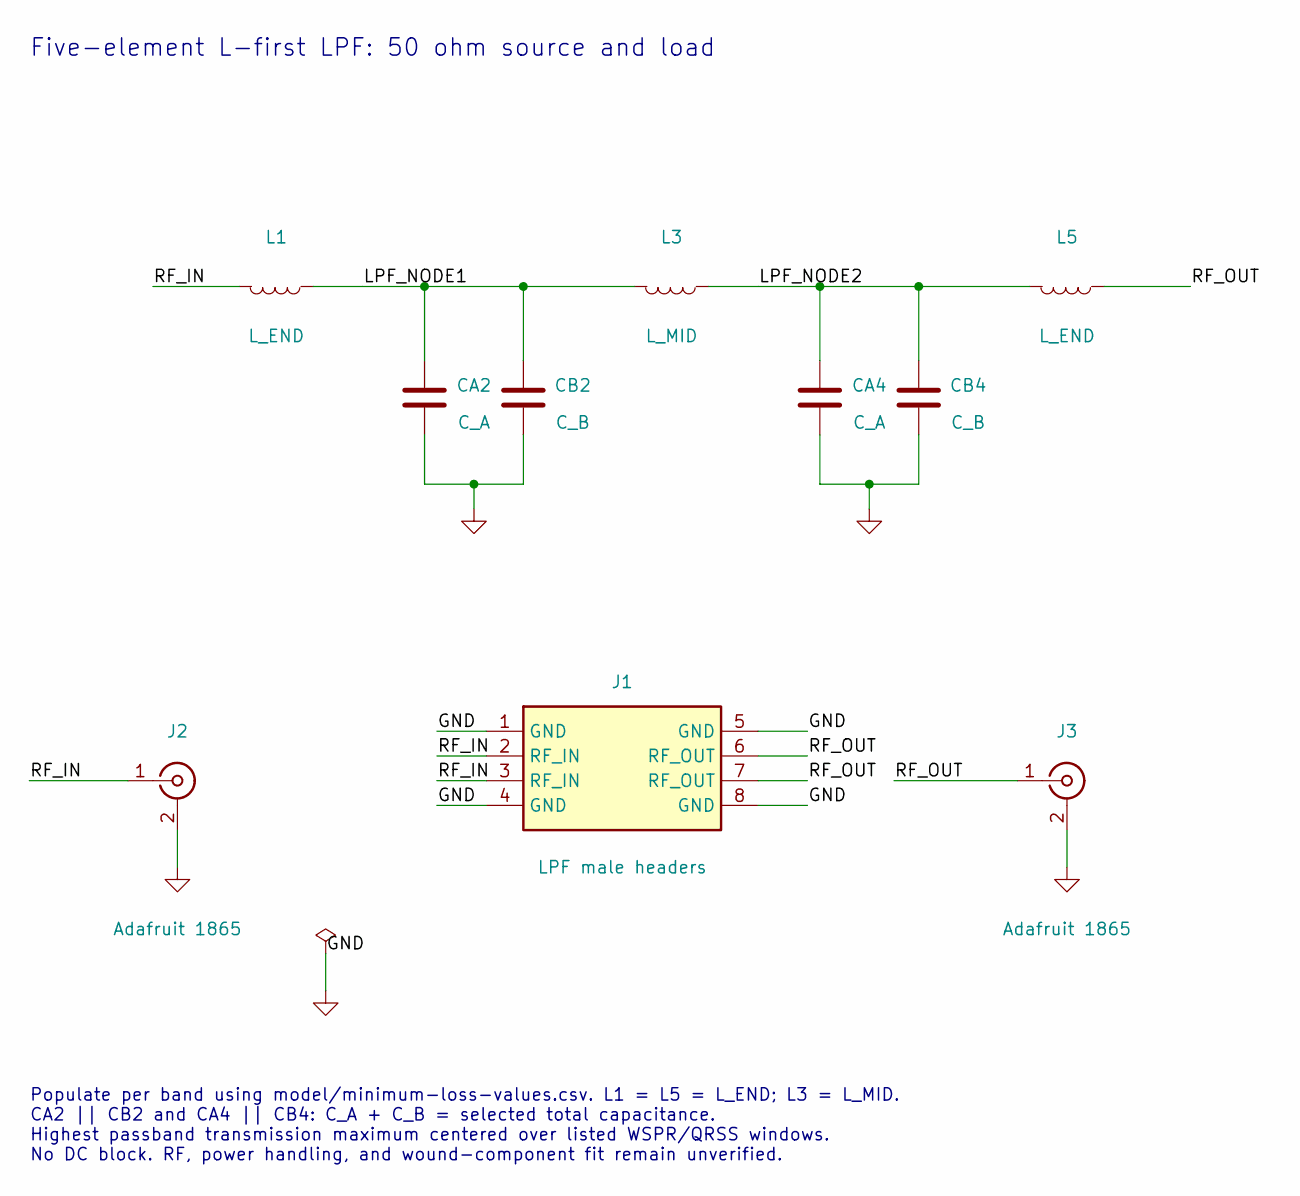
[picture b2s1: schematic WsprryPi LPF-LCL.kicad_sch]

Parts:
CA2, CA4: C_A; C_Disc_D3.0mm_W1.6mm_P2.50mm
CB2, CB4: C_B; C_Disc_D3.0mm_W1.6mm_P2.50mm
J1: LPF male headers; LPF_HeaderPair_Male_2x1x04_P2.54mm_S33.02mm
J2, J3: Adafruit 1865; SMA_Adafruit_1865_EdgeMount; MPN 1865
L1, L5: L_END; L_Axial_Horiz_Torroid_Vert_12mm_D5mm_P10.2mm
L3: L_MID; L_Axial_Horiz_Torroid_Vert_12mm_D5mm_P10.2mm

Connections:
/LPF_NODE1: CA2.2, CB2.2, L1.1, L3.2
/LPF_NODE2: CA4.2, CB4.2, L3.1, L5.2
/RF_IN: J1.2 (RF_IN), J1.3 (RF_IN), J2.1 (In), L1.2
/RF_OUT: J1.6 (RF_OUT), J1.7 (RF_OUT), J3.1 (In), L5.1
GND: CA2.1, CA4.1, CB2.1, CB4.1, J1.1 (GND), J1.4 (GND), J1.5 (GND), J1.8 (GND), J2.2 (Ext), J3.2 (Ext)

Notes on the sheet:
Five-element L-first LPF: 50 ohm source and load
Populate per band using model/minimum-loss-values.csv. L1 = L5 = L_END; L3 = L_MID. CA2 || CB2 and CA4 || CB4: C_A + C_B = selected total capacitance. Highest passband transmission maximum centered over listed WSPR/QRSS windows. No DC block. RF, power handling, and wound-component fit remain unveri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

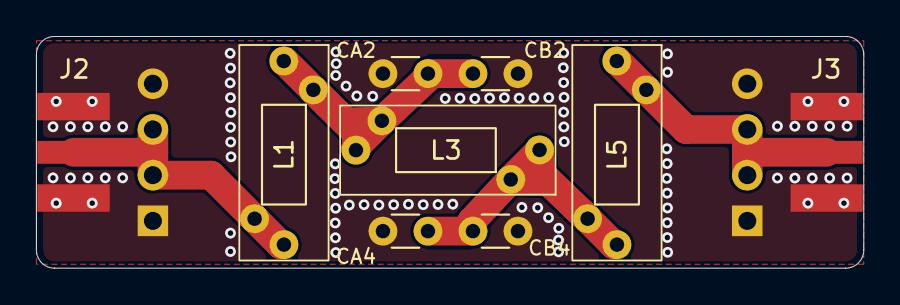
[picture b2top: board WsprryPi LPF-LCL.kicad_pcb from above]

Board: 2 copper layers, 46.0 x 12.9 mm, 10 parts (1 on the bottom side), 5 nets.

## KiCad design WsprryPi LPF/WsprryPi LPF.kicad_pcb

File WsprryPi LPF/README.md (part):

# WsprryPi LPF Board

A hand-assembled, seven-element low-pass filter (LPF) board with three series inductors and four shunt-capacitor positions. Each shunt position supports two parallel capacitors.

**Design status: in development; not yet qualified for production or RF use.** KiCad checks report zero DRC violations, zero unconnected items, and zero schematic-parity issues. Assembly fit and measured RF performance remain unverified.

## Project files

Open [WsprryPi LPF.kicad_pro](WsprryPi%20LPF.kicad_pro) in KiCad 10.0.1 or newer. The KiCad sources are authoritative; generate any required schematic export from the current source revision.

The [project libraries](libraries/README.md) contain every symbol and footprint used by the design, plus available 3D models. Keep the `libraries/` folder and library tables with the project; their `${KIPRJMOD}` paths resolve within this directory. Library documentation covers connector options, model limitations, sources, and licenses.

The [filter workbook](./LPF-Values.xlsx) lists standard E96/E24 values for a seven-element, 1 dB Chebyshev C-L-C ladder and its ideal, lossless 50-ohm response. Parallel E24 capacitor pairs are used where their sum better approaches the target value. The 3 dB cutoff and fundamental-loss columns are calculated from the listed installed values, not the unrounded prototype values. The board does not implement a DC-blocking capacitor.

The 2 m filter is fully specified as `47.5 pF – 60.4 nH – 68.1 pF – 63.4 nH – 68.1 pF – 60.4 nH – 47.5 pF`. Its modeled 3 dB cutoff is 148.279504 MHz and its modeled loss at the 144.4901 MHz upper WSPR edge is 0.376 dB. The row uses the 144.4899–144.4901 MHz transmit band in the [WSPR frequency list](https://www.wsprnet.org/drupal/sites/wsprnet.org/files/wspr-qrg.pdf). Only the 2 m QRSS frequency cell is blank; no 2 m QRSS operating frequency is asserted by this project.

The [circuit-modeling study](../WsprryPi%20LPF-LCL/model/README.md), now maintained with the independent [WsprryPi LPF-LCL project](../WsprryPi%20LPF-LCL/README.md), reproduces this workbook's responses and compares seven- and five-element L-first alternatives. It includes minimum-loss WSPR/QRSS tuning, component targets, ideal harmonic rejection, illustrative coil-Q sensitivity, and shared-band limitations. The filter topology and band-value workbook remain unchanged by the connector replacement.

## Assembly

The input and output connectors are hand-fitted male 1×4 headers with 2.54 mm pin pitch. The current schematic and PCB represent both headers as one component, **J1**, using the project-local paired-header footprint on the underside (B.Cu), with **33.02 mm centerline spacing**. The local symbol and footprint are named `LPF_HeaderPair_Male_2x1x04_P2.54mm_S33.02mm`; the matching BS170-board sockets use `LPF_HeaderPair_Female_2x1x04_P2.54mm_S33.02mm`. No manufacturer or purchasing part number is specified. The connector and filter components are excluded from the BOM; a default BOM export is not a complete hand-assembly purchasing list.

### Optional Adafruit edge-launch SMA connectors

J2 (RF_IN) and J3 (RF_OUT) are hand-soldered **[Adafruit 1865](https://www.adafruit.com/product/1865)** 50 Ω female edge-launch SMA connectors for **1.6 mm PCBs**. Pin 1 connects to the corresponding RF header net; pin 2 comprises the ground fingers on both copper faces. The paired underside headers retain their original 33.02 mm spacing and every hole location. SMAs remain included in the BOM; headers and filter components retain their previous exclusions.

The outline remains **45.96 × approximately 12.873 mm**, with the original rounded corners and 1.60 mm stackup. The connector edge datums are J2 at **(114.00, 99.12) mm, −90°**, and J3 at **(159.96, 99.12) mm, +90°**. The footprint points outward along local +Y. Both axes remain at Y = 99.12 mm; the new origins lie on the board ends rather than at the former Samtec center-pad origins. The RF land centers are X = 116.057 mm and X = 157.903 mm. Existing launch traces have their endpoints repaired to those centers.

Each independent local library contains `SMA_Adafruit_1865_EdgeMount`, adapted from the repository's Adafruit footprint and checked against the published public-domain `SMA_EDGELAUNCH` land pattern and [Adafruit drawing](https://cdn-shop.adafruit.com/product-files/1865/C2387-001_datasheet.pdf). Lands are 1.27 mm wide for signal and 1.524 mm wide for ground, at 2.54 mm transverse spacing. Their 4.014 mm length retains a **0.05 mm copper setback** from the physical board edge. No solder-paste apertures are provided; solder the top signal/ground fingers and underside ground fingers by hand.

The project-local `.kicad_dru` file provides a **0 mm minimum edge-clearance override only for pads of J2/J3**. It handles either object order in the DRC comparison. All other copper retains the original **0.50 mm global edge clearance**, and pad-to-pad, via, hole, and other manufacturing rules are unchanged. The small physical setback keeps the lands clear of the drawn Edge.Cuts stroke; this is not a blanket DRC exclusion or severity change. Confirm that the chosen board fabricator accepts these near-edge copper lands.

The attached project-local `SMA_Adafruit_1865_Preview.wrl` is an illustrative repository-owned model, not supplier CAD. Adafruit product 1865 is specified for 1.6 mm boards, matching the saved stackup. Confirm connector slot tolerance, solder access on both faces, external body/enclosure clearance, and actual fit before ordering. The SMA body projects beyond the outline. Launch impedance, insertion loss, and RF performance remain unmeasured.

### Connector pinouts and QRP Labs compatibility

J1 combines the input and output header rows:

| J1 header row | Ground pads | RF pads |
| --- | --- | --- |
| Input | 1 and 4 | 2 and 3, RF_IN |
| Output | 5 and 8 | 6 and 7, RF_OUT |

These are KiCad pad numbers, not the physical position numbers used for adaptation below. Looking down onto the component side of the saved board, the input row runs **4–3–2–1** and the output row runs **8–7–6–5** from the upper board edge to the lower edge because J1 is mounted underneath.

This design was inspired by the QRP Labs method of interchangeable plug-in LPFs, but it uses a **different pinout and is not directly compatible with QRP Labs LPFs**. The WsprryPi pinout groups the two RF contacts in the middle and brackets them with signal ground contacts. It was created to allow a denser signal path with nearby ground returns, with the intent of improving RF performance; that benefit has not yet been established by measurements on this board.

The diagram numbers **physical positions 1–4 from top to bottom**, independently of KiCad pad numbering. Both header rows have the illustrated pattern. QRP Labs uses RF–RF–GND–GND in the illustrated orientation, while WsprryPi uses GND–RF–RF–GND. See the [QRP Labs assembly drawing, page 3](https://qrp-labs.com/images/lpfkit/assembly_A4.pdf).

For the orientation shown, an operator may remove pins at **physical positions 1 and 3 from both headers of the module being adapted—four pins total**. The remaining positions **2 and 4 provide RF and ground**, respectively. This applies electrically to adapting a WsprryPi module to a QRP Labs socket or a QRP Labs module to a WsprryPi socket, provided the mechanical spacing and fit match. The WsprryPi paired header uses 33.02 mm spacing.

**Orientation matters:** turning the module end-for-end reverses both rows and changes which positions conflict. The WsprryPi GND–RF–RF–GND pinout and symmetric filter topology permit electrical connection in either direction in a matching WsprryPi socket. The cross-compatible two-contact arrangement is orientation-specific: after modification, use only the orientation shown for the adapted target socket. This is especially important because the unmodified outline alone does not establish a safe orientation.

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
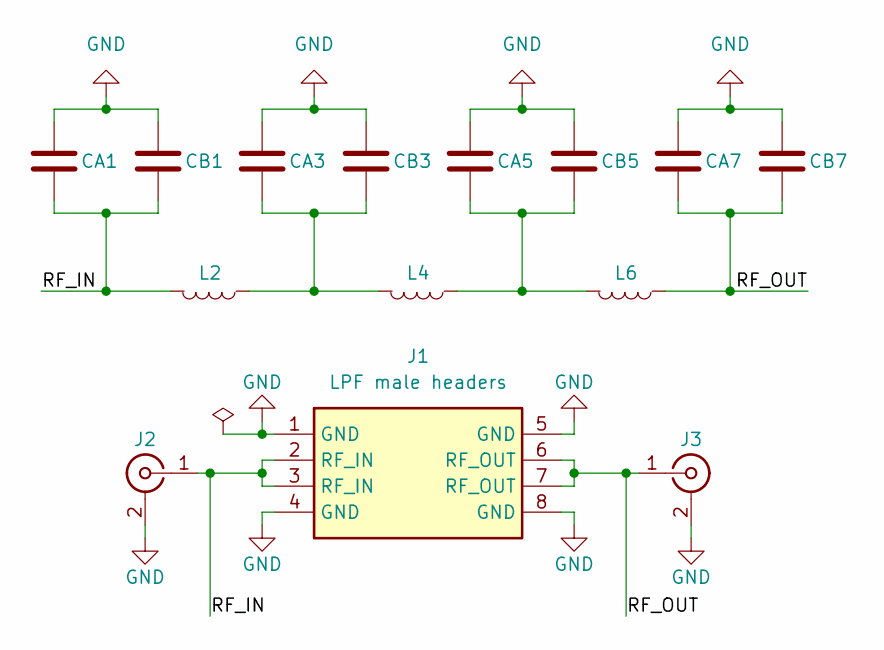
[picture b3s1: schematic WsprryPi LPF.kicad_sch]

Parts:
CA1, CA3, CA5, CA7: C; C_Disc_D3.0mm_W1.6mm_P2.50mm
CB1, CB3, CB5, CB7: C; C_Disc_D3.0mm_W1.6mm_P2.50mm
J1: LPF male headers; LPF_HeaderPair_Male_2x1x04_P2.54mm_S33.02mm
J2, J3: Adafruit 1865; SMA_Adafruit_1865_EdgeMount; MPN 1865
L2, L4, L6: L; L_Axial_Horiz_Torroid_Vert_12mm_D5mm_P10.2mm

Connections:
/RF_IN: CA1.2, CB1.2, J1.2 (RF_IN), J1.3 (RF_IN), J2.1 (In), L2.2
/RF_OUT: CA7.2, CB7.2, J1.6 (RF_OUT), J1.7 (RF_OUT), J3.1 (In), L6.1
GND: CA1.1, CA3.1, CA5.1, CA7.1, CB1.1, CB3.1, CB5.1, CB7.1, J1.1 (GND), J1.4 (GND), J1.5 (GND), J1.8 (GND), J2.2 (Ext), J3.2 (Ext)
unnamed: CA3.2, CB3.2, L2.1, L4.2
unnamed: CA5.2, CB5.2, L4.1, L6.2

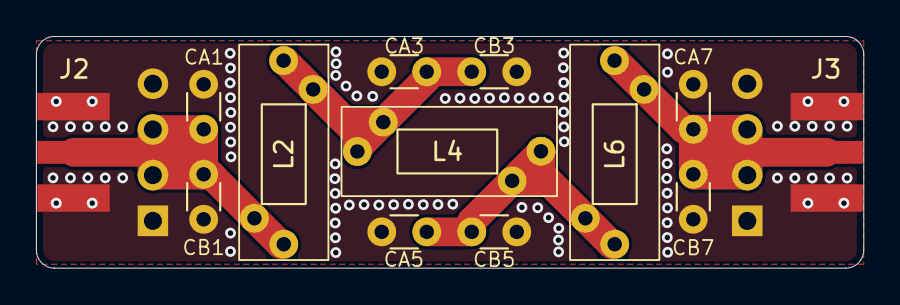
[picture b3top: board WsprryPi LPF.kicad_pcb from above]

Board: 2 copper layers, 46.0 x 12.9 mm, 14 parts (1 on the bottom side), 5 nets.

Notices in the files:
Relay-Switched LPF/README.md:
Newly drawn documentation, library geometry, nominal previews, and generator code use the repository [MIT license](../LICENSE.md).
WsprryPi LPF-LCL/README.md:
Repository-owned work follows the [MIT license](../LICENSE.md). KiCad-derived assets retain their [third-party attribution and library license](libraries/README.md#sources-and-licenses).
parts and their libraries:
Adafruit 1865; SMA_EDGELAUNCH converted from Adafruit Eagle Library (Public Domain), https://github.com/adafruit/Adafruit-Eagle-Library ; www.adafruit.com ; origin at PCB edge; nominal 1.6mm PCB
